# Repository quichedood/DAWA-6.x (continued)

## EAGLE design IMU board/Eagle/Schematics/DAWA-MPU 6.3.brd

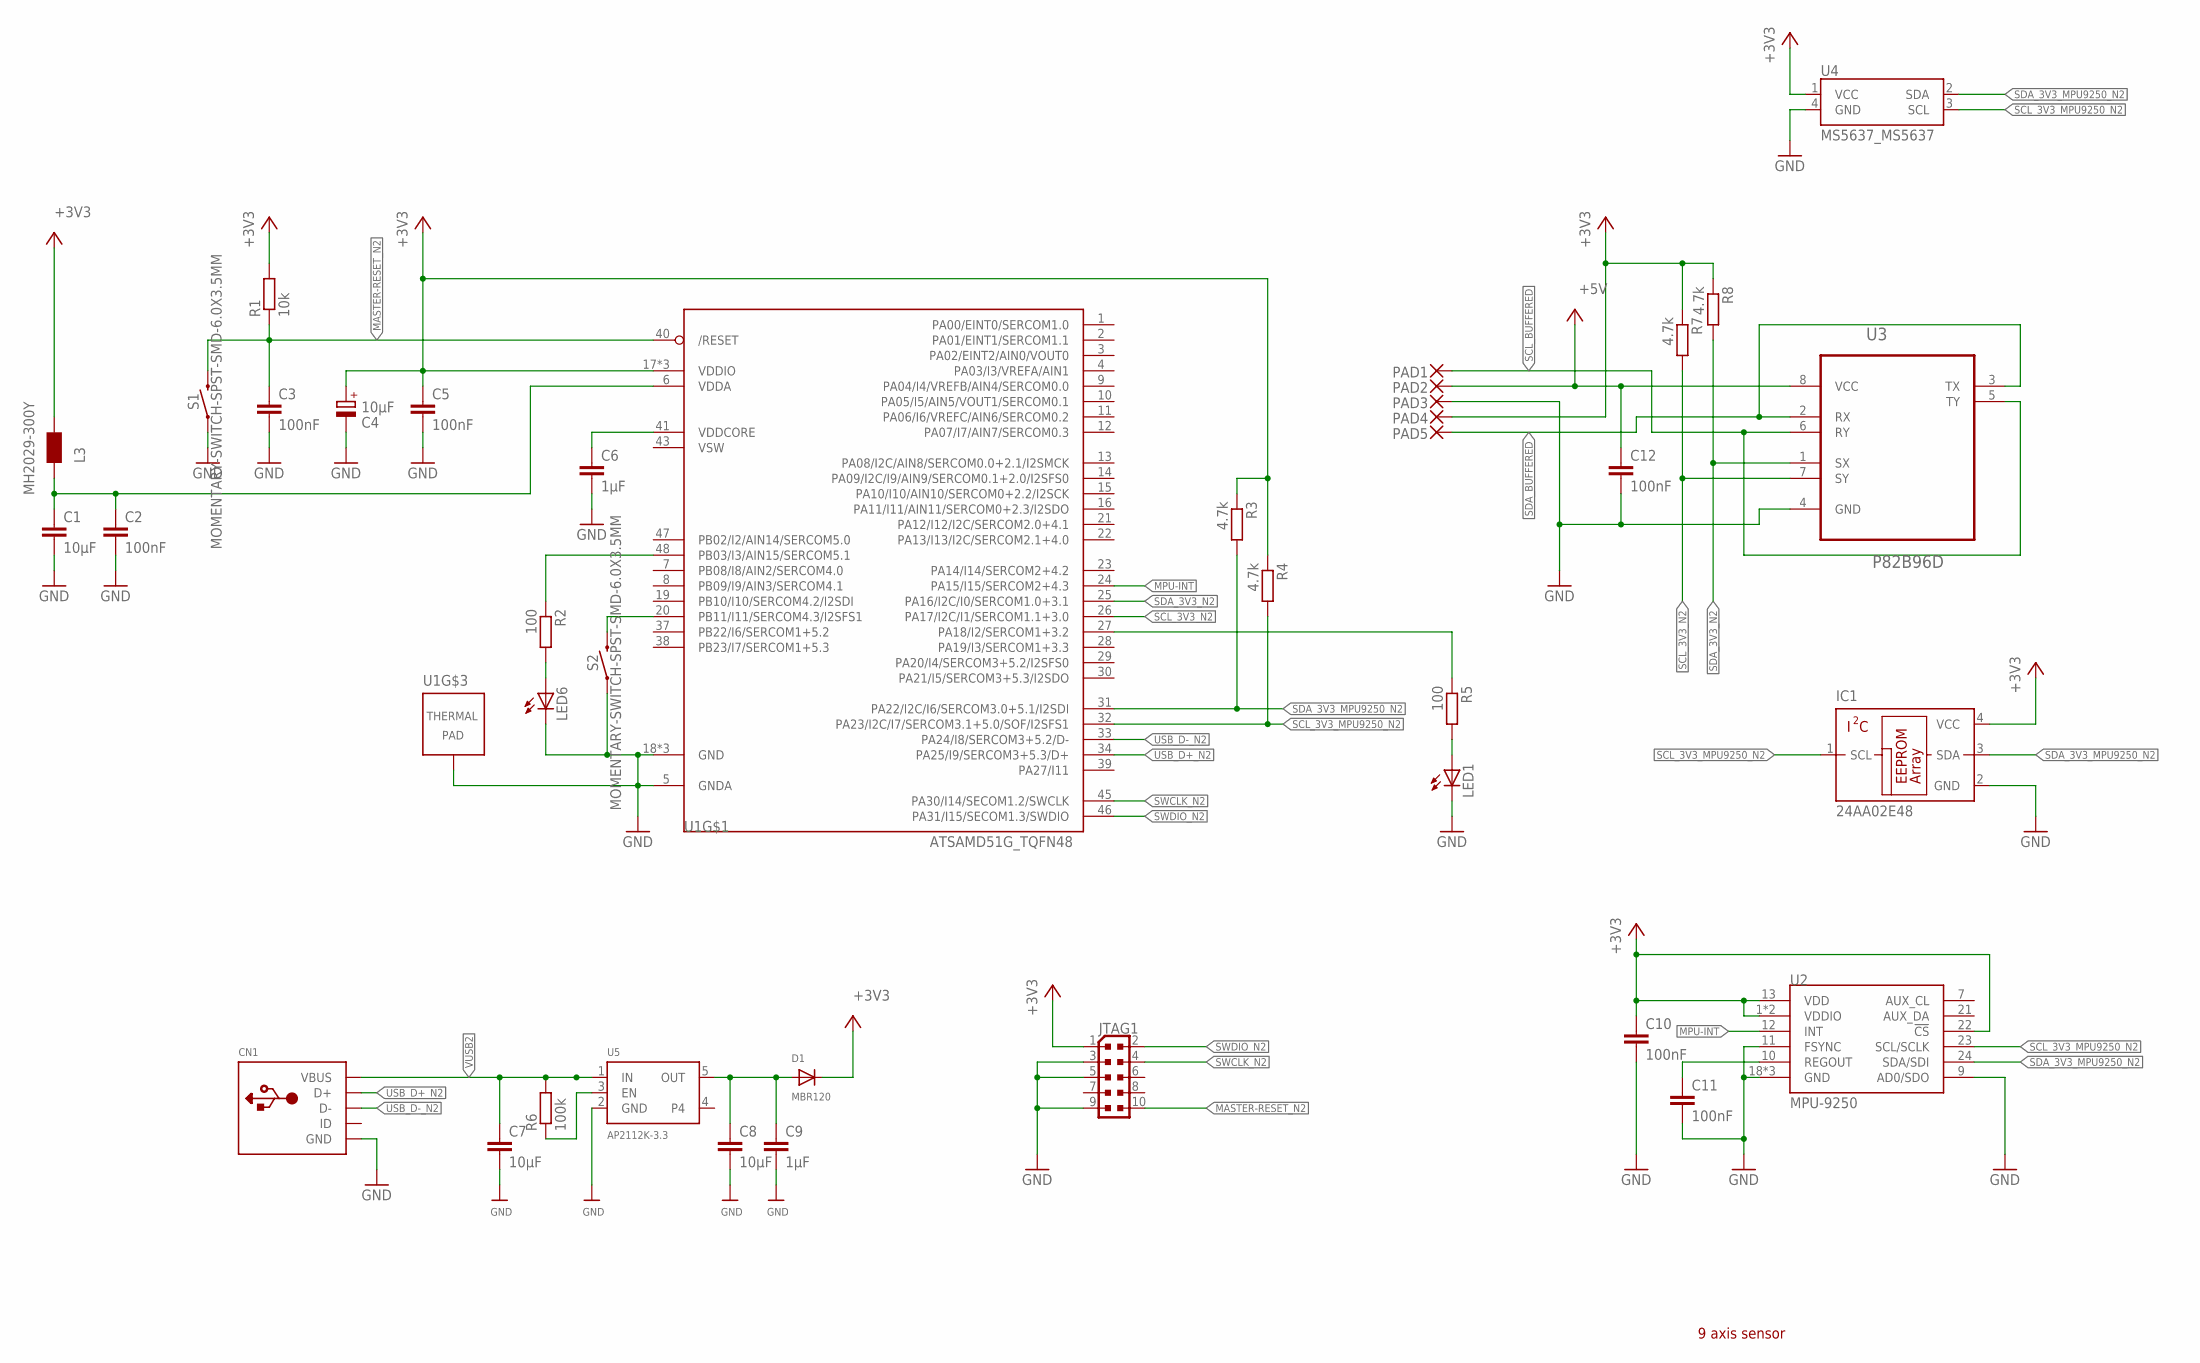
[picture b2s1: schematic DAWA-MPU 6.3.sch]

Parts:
C1: 10µF; C0805
C2, C3, C5, C10, C11, C12: 100nF; C0603
C4: 10µF; SMC_B
C6, C9: 1µF; C0603
C7, C8: 10µF; C0603
CN1: USB; USB-MINIB-DAWA
D1: MBR120; SOD-123FL
IC1: 24AA02E48; SOT23-5L
JTAG1: PINHEAD_PINHD-2X5PASSO127; PINHEAD_2X05_127
L3: MH2029-300Y; 0805
LED1, LED6: LEDCHIPLED_1206; CHIPLED_1206
PAD1, PAD2, PAD3, PAD4, PAD5: WIREPAD1,6/0,9; 1,6/0,9
R1: 10k; R0603
R2, R5: 100; R0603
R3, R4, R7, R8: 4.7k; R0603
R6: 100k; R0603
S1, S2: MOMENTARY-SWITCH-SPST-SMD-6.0X3.5MM; TACTILE_SWITCH_SMD_6.0X3.5MM
U1: ATSAMD51G_TQFN48; TQFN48_7MM
U2: MPU-9250; QFN24_PAD
U3: P82B96D; SOIC127P600X175-8N
U4: MS5637_MS5637
U5: AP2112K-3.3; SOT23-5

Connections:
+3V1: R2.1, U1.48 (PB03/I3/AIN15/SERCOM5.1)
+3V2: R5.1, U1.27 (PA18/I2/SERCOM1+3.2)
+3V3: C4.+, C5.1, C10.1, D1.C, IC1.4 (VCC), JTAG1.1, L3.1, PAD4.1, R1.2, R3.1, R4.1, R7.1, R8.1, U1.17 (VDDIO), U1.36 (VDDIO), U1.44 (VDDIO), U2.1 (VDDIO), U2.8 (VDDIO), U2.13 (VDD), U2.22 (!CS), U4.1 (VCC)
+5V: C12.1, PAD2.1, U3.8 (VCC)
GND: C1.2, C2.2, C3.2, C4.-, C5.2, C6.2, C7.2, C8.2, C9.2, C10.2, C11.2, C12.2, CN1.GND, CN1.GND1 (GND), CN1.GND2 (GND), IC1.2 (GND), JTAG1.3, JTAG1.5, JTAG1.9, LED1.C, LED6.C, PAD3.1, S1.1, S2.1, U1.5 (GNDA), U1.18 (GND), U1.35 (GND), U1.42 (GND), U1.THERMAL (TP), U2.9 (AD0/SDO), U2.11 (FSYNC), U2.18 (GND), U2.20 (GND), U2.CENTER (GND), U3.4 (GND), U4.4 (GND), U5.2 (GND)
MASTER-RESET_N2: C3.1, JTAG1.10, R1.1, S1.2, U1.40 (/RESET)
MPU-INT: U1.24 (PA15/I15/SERCOM2+4.3), U2.12 (INT)
unnamed: LED1.A, R5.2
unnamed: C6.1, U1.41 (VDDCORE)
unnamed: S2.2, U1.20 (PB11/I11/SERCOM4.3/I2SFS1)
unnamed: LED6.A, R2.2
unnamed: R6.1, U5.3 (EN)
OUT: C8.1, C9.1, D1.A, U5.5 (OUT)
REGOUT: C11.1, U2.10 (REGOUT)
SCL_3V3_MPU9250_N2: IC1.1 (SCL), R4.2, U1.32 (PA23/I2C/I7/SERCOM3.1+5.0/SOF/I2SFS1), U2.23 (SCL/SCLK), U4.3 (SCL)
SCL_3V3_N2: R7.2, U1.26 (PA17/I2C/I1/SERCOM1.1+3.0), U3.7 (SY)
SCL_BUFFERED: PAD1.1, U3.5 (TY), U3.6 (RY)
SDA_3V3_MPU9250_N2: IC1.3 (SDA), R3.2, U1.31 (PA22/I2C/I6/SERCOM3.0+5.1/I2SDI), U2.24 (SDA/SDI), U4.2 (SDA)
SDA_3V3_N2: R8.2, U1.25 (PA16/I2C/I0/SERCOM1.0+3.1), U3.1 (SX)
SDA_BUFFERED: PAD5.1, U3.2 (RX), U3.3 (TX)
SWCLK_N2: JTAG1.4, U1.45 (PA30/I14/SECOM1.2/SWCLK)
SWDIO_N2: JTAG1.2, U1.46 (PA31/I15/SECOM1.3/SWDIO)
USB_D+_N2: CN1.D+, U1.34 (PA25/I9/SERCOM3+5.3/D+)
USB_D-_N2: CN1.D-, U1.33 (PA24/I8/SERCOM3+5.2/D-)
VDDANA1: C1.1, C2.1, L3.2, U1.6 (VDDA)
VSW: U1.43 (VSW)
VUSB2: C7.1, CN1.VBUS, R6.2, U5.1 (IN)

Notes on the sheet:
9 axis sensor

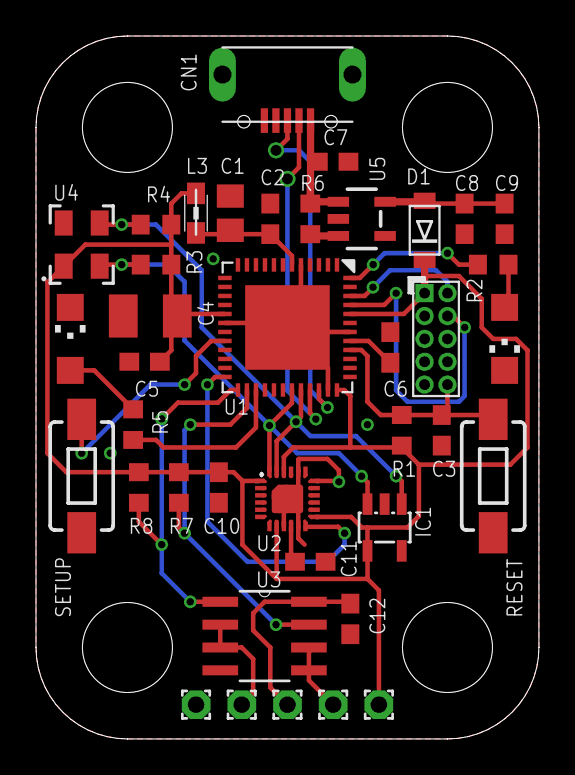
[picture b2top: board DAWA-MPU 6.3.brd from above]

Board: 2 copper layers, 27.9 x 39.1 mm, 39 parts (0 on the bottom side), 26 nets.

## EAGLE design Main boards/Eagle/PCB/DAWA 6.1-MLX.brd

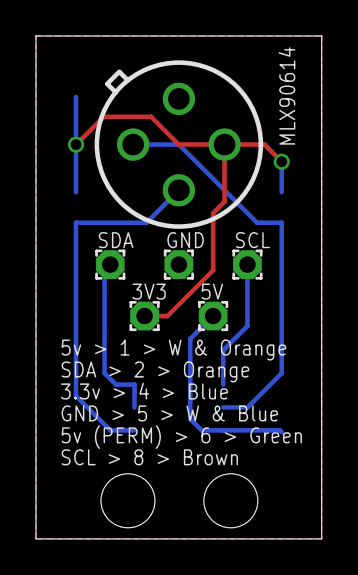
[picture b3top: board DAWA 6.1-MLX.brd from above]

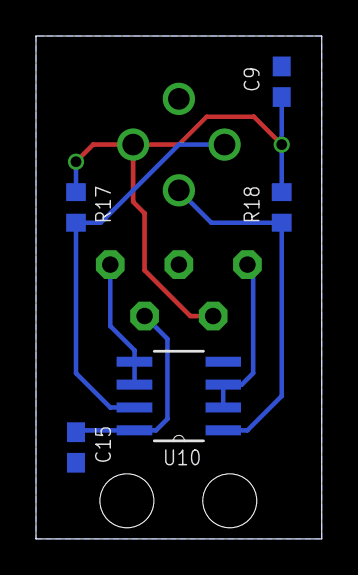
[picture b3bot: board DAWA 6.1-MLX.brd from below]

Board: 2 copper layers, 15.9 x 27.9 mm, 11 parts (5 on the bottom side), 7 nets.

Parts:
C9, C15: 100nF; C0603
MLX90614: MLX90614; TO-39
PAD6, PAD7, PAD8, PAD9, PAD10: 1,6/0,9
R17, R18: 4.7k; R0603
U10: P82B96D; SOIC127P600X175-8N

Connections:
+3V3: C9.2, MLX90614.P$3, PAD9.1, R17.1, R18.1
+5V: C15.1, PAD7.1, U10.8
GND: C9.1, C15.2, MLX90614.P$4, PAD8.1, U10.4
SCL_BUFFERED: PAD6.1, U10.5, U10.6
SCL_MLX_SENSOR: MLX90614.P$1, R17.2, U10.7
SDA_BUFFERED: PAD10.1, U10.2, U10.3
SDA_MLX_SENSOR: MLX90614.P$2, R18.2, U10.1

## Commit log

2019-07-15 :circus_tent: Added .gitattributes & .gitignore files
2019-07-15 DAWA 6.1
    Initial release
2019-07-22 Add prices
2019-12-16 v6.3
2020-11-03 Add PDF schematics
